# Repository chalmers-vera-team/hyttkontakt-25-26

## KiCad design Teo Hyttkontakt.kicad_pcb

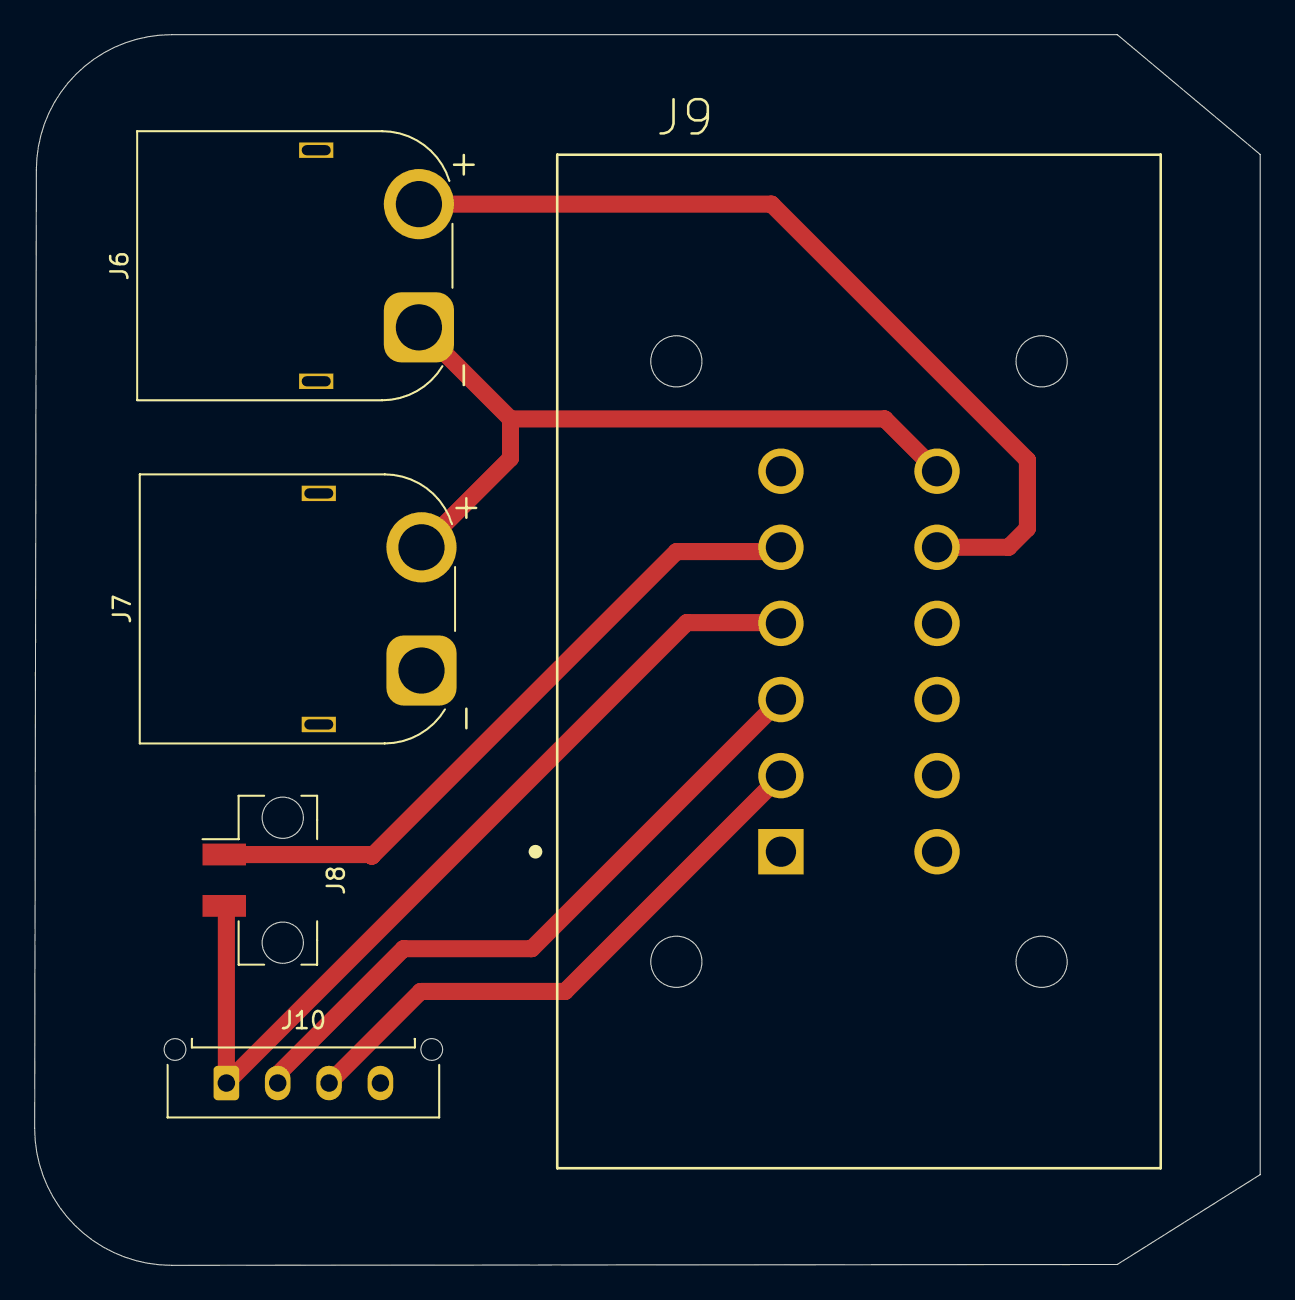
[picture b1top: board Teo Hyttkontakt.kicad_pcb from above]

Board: 2 copper layers, 71.6 x 71.9 mm, 5 parts (0 on the bottom side), 8 nets.

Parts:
J6, J7: Conn_01x02; AMASS_XT60PW-M_1x02_P7.20mm_Horizontal
J8: Conn_01x02; Molex_Micro-Fit_3.0_43650-0221_1x02_P3.00mm_Vertical
J9: Conn_01x08; TE_DT15-12PA
J10: Conn_01x04; Molex_Micro-Fit_3.0_43650-0415_1x04_P3.00mm_Vertical

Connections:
+12V: J8.2, J9.4, J10.1
+BATT: J6.2, J9.8
CAN High: J9.3, J10.2
CAN Low: J9.2, J10.3
Dead Man's Switch: J8.1, J9.5
GND: J9.1, J10.4
GNDPWR: J7.1, J9.6
Relay: J6.1, J7.2, J9.7

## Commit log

2025-12-14 La in ny projekt
